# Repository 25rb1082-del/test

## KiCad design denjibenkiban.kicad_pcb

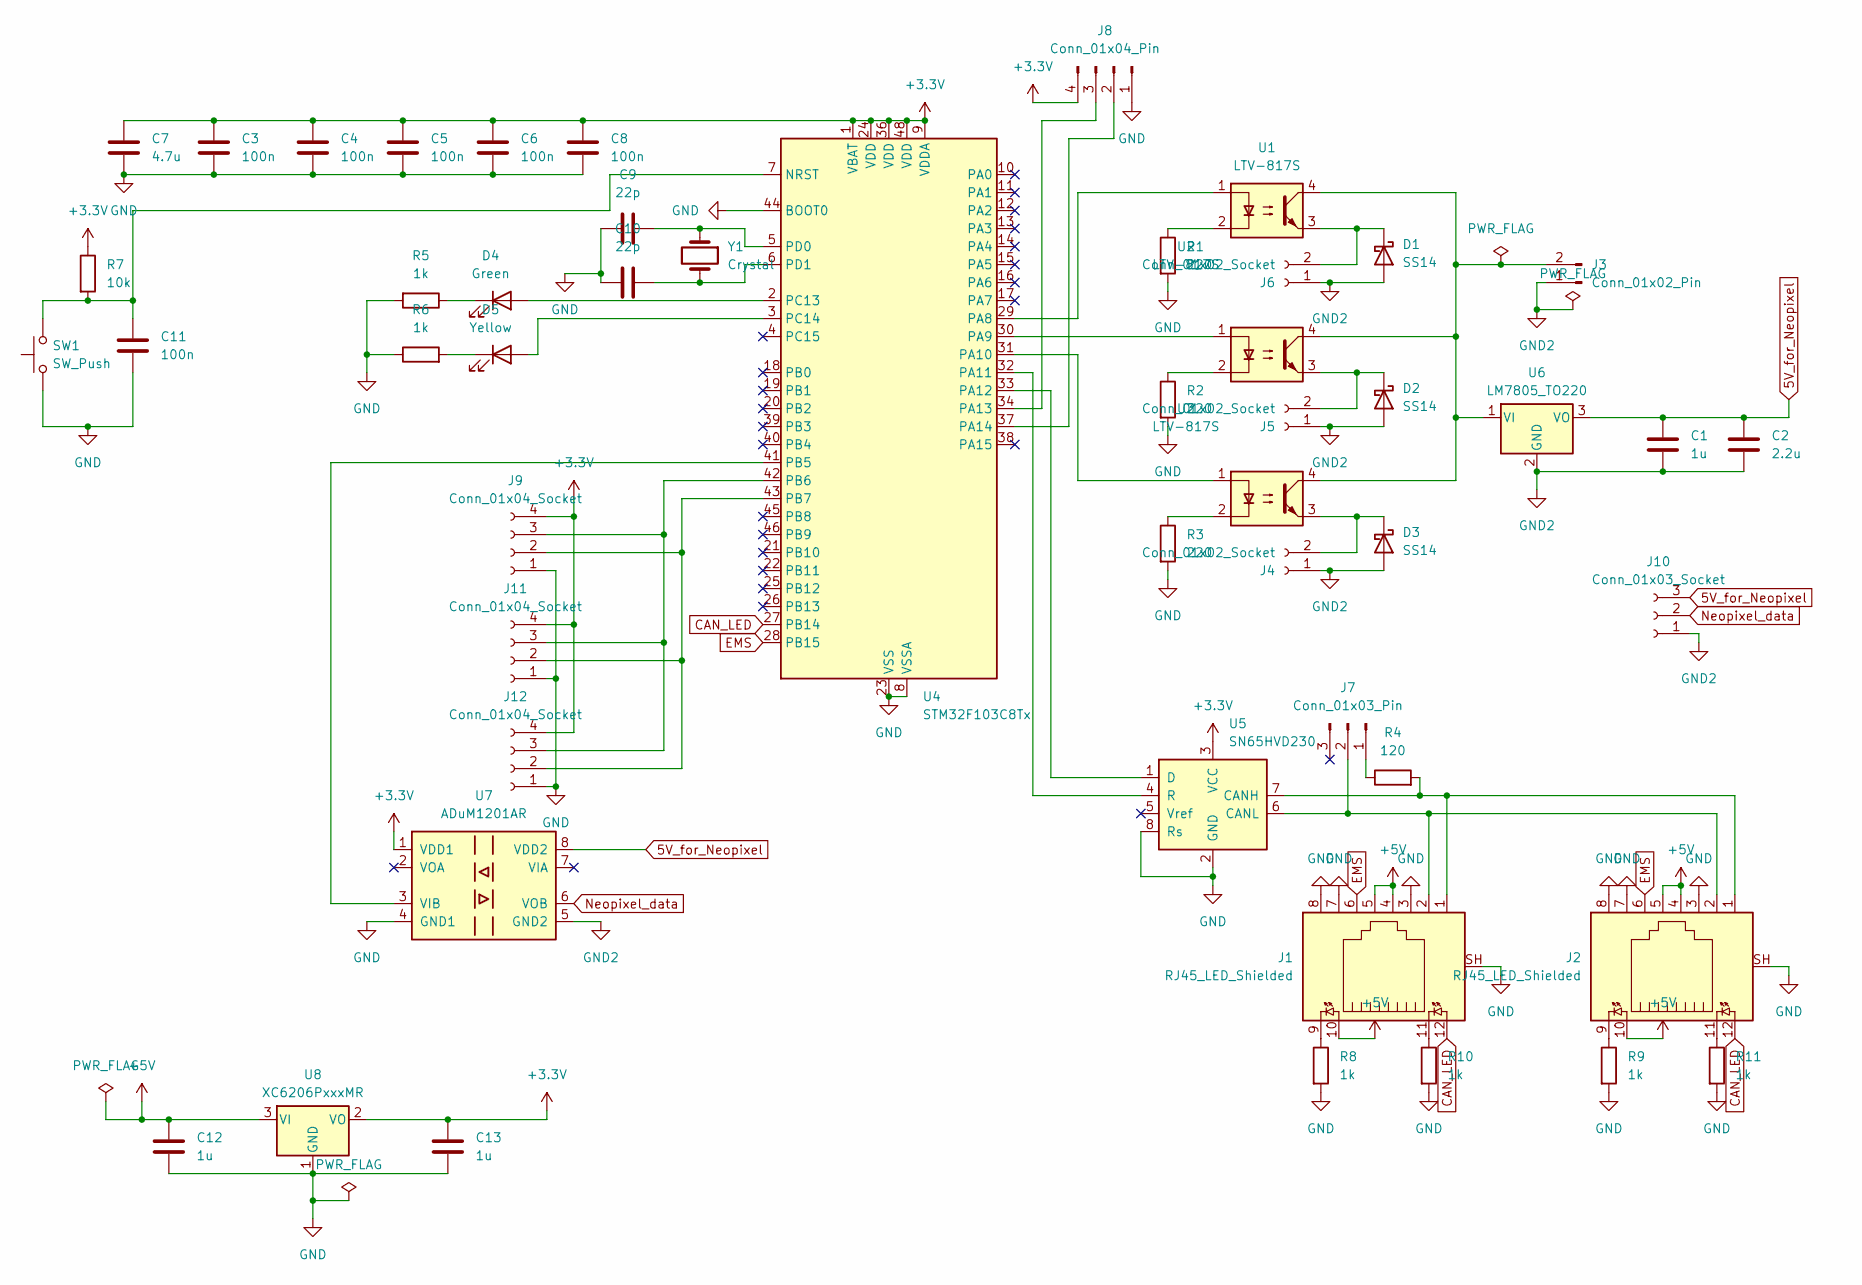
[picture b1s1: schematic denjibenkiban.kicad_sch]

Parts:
C1, C12, C13: 1u; C_0603_1608Metric
C2: 2.2u; C_0603_1608Metric
C3, C4, C5, C6, C8, C11: 100n; C_0603_1608Metric
C7: 4.7u; C_0603_1608Metric
C9, C10: 22p; C_0603_1608Metric
D1, D2, D3: SS14; D_SMA
D4: Green; LED_0805_2012Metric
D5: Yellow; LED_0805_2012Metric
J1, J2: RJ45_LED_Shielded; RJ45_Amphenol_RJHSE538X
J3: Conn_01x02_Pin; AMASS_XT30U-F_1x02_P5.0mm_Vertical
J4, J5, J6: Conn_01x02_Socket; JST_XH_B2B-XH-A_1x02_P2.50mm_Vertical
J7: Conn_01x03_Pin; PinHeader_1x03_P2.54mm_Vertical
J8: Conn_01x04_Pin; PinHeader_1x04_P2.54mm_Vertical
J9, J11, J12: Conn_01x04_Socket; JST_XH_B4B-XH-A_1x04_P2.50mm_Vertical
J10: Conn_01x03_Socket; JST_XH_B3B-XH-A_1x03_P2.50mm_Vertical
R1, R2, R3: 220; R_0603_1608Metric
R4: 120; R_0603_1608Metric
R5, R6, R8, R9, R10, R11: 1k; R_0603_1608Metric
R7: 10k; R_0603_1608Metric
SW1: SW_Push; SW_TS-1088-AR02016
U1, U2, U3: LTV-817S; SMDIP-4_W9.53mm
U4: STM32F103C8Tx; LQFP-48_7x7mm_P0.5mm
U5: SN65HVD230; SOIC-8_3.9x4.9mm_P1.27mm
U6: LM7805_TO220; TO-220-3_Vertical
U7: ADuM1201AR; SOIC-8_3.9x4.9mm_P1.27mm
U8: XC6206PxxxMR; SOT-23-3
Y1: Crystal; Crystal_SMD_5032-2Pin_5.0x3.2mm

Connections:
5V_for_Neopixel: C1.1, C2.1, J10.3, U6.3 (VO), U7.8 (VDD2)
+3.3V: C3.1, C4.1, C5.1, C6.1, C7.1, C8.1, C13.1, J8.4, J9.4, J11.4, J12.4, R7.1, U4.1 (VBAT), U4.9 (VDDA), U4.24 (VDD), U4.36 (VDD), U4.48 (VDD), U5.3 (VCC), U7.1 (VDD1), U8.2 (VO)
+5V: C12.1, J1.4, J1.5, J1.10, J2.4, J2.5, J2.10, U8.3 (VI)
CAN_LED: J1.12, J2.12, U4.27 (PB14)
EMS: J1.6, J2.6, U4.28 (PB15)
GND: C3.2, C4.2, C5.2, C6.2, C7.2, C8.2, C9.2, C10.2, C11.1, C12.2, C13.2, J1.3, J1.7, J1.8, J1.SH, J2.3, J2.7, J2.8, J2.SH, J8.1, J9.1, J11.1, J12.1, R1.2, R2.2, R3.2, R5.2, R6.1, R8.2, R9.2, R10.2, R11.2, SW1.1, U4.8 (VSSA), U4.23 (VSS), U4.35 (VSS), U4.44 (BOOT0), U4.47 (VSS), U5.2 (GND), U5.8 (Rs), U7.4 (GND1), U8.1 (GND)
GND2: C1.2, C2.2, D1.2 (A), D2.2 (A), D3.2 (A), J3.1, J4.1, J5.1, J6.1, J10.1, U6.2 (GND), U7.5 (GND2)
Neopixel_data: J10.2, U7.6 (VOB)
unnamed: D1.1 (K), J6.2, U1.3
unnamed: D2.1 (K), J5.2, U2.3
unnamed: D3.1 (K), J4.2, U3.3
unnamed: D4.2 (A), U4.2 (PC13)
unnamed: D4.1 (K), R5.1
unnamed: D5.2 (A), U4.3 (PC14)
unnamed: D5.1 (K), R6.2
unnamed: J1.9, R8.1
unnamed: J1.11, R10.1
unnamed: J2.9, R9.1
unnamed: J2.11, R11.1
unnamed: J3.2, U1.4, U2.4, U3.4, U6.1 (VI)
unnamed: J7.1, R4.1
unnamed: J1.2, J2.2, J7.2, U5.6 (CANL)
unnamed: J8.2, U4.37 (PA14)
unnamed: J8.3, U4.34 (PA13)
unnamed: J9.2, J11.2, J12.2, U4.43 (PB7)
unnamed: J9.3, J11.3, J12.3, U4.42 (PB6)
unnamed: R1.1, U1.2
unnamed: R2.1, U2.2
unnamed: R3.1, U3.2
unnamed: C11.2, R7.2, SW1.2, U4.7 (NRST)
unnamed: U1.1, U4.29 (PA8)
unnamed: U2.1, U4.30 (PA9)
unnamed: U3.1, U4.31 (PA10)
unnamed: U4.32 (PA11), U5.4 (R)
unnamed: U4.33 (PA12), U5.1 (D)
unnamed: U4.41 (PB5), U7.3 (VIB)
unnamed: C9.1, U4.5 (PD0), Y1.1
unnamed: C10.1, U4.6 (PD1), Y1.2
unnamed: J1.1, J2.1, R4.2, U5.7 (CANH)

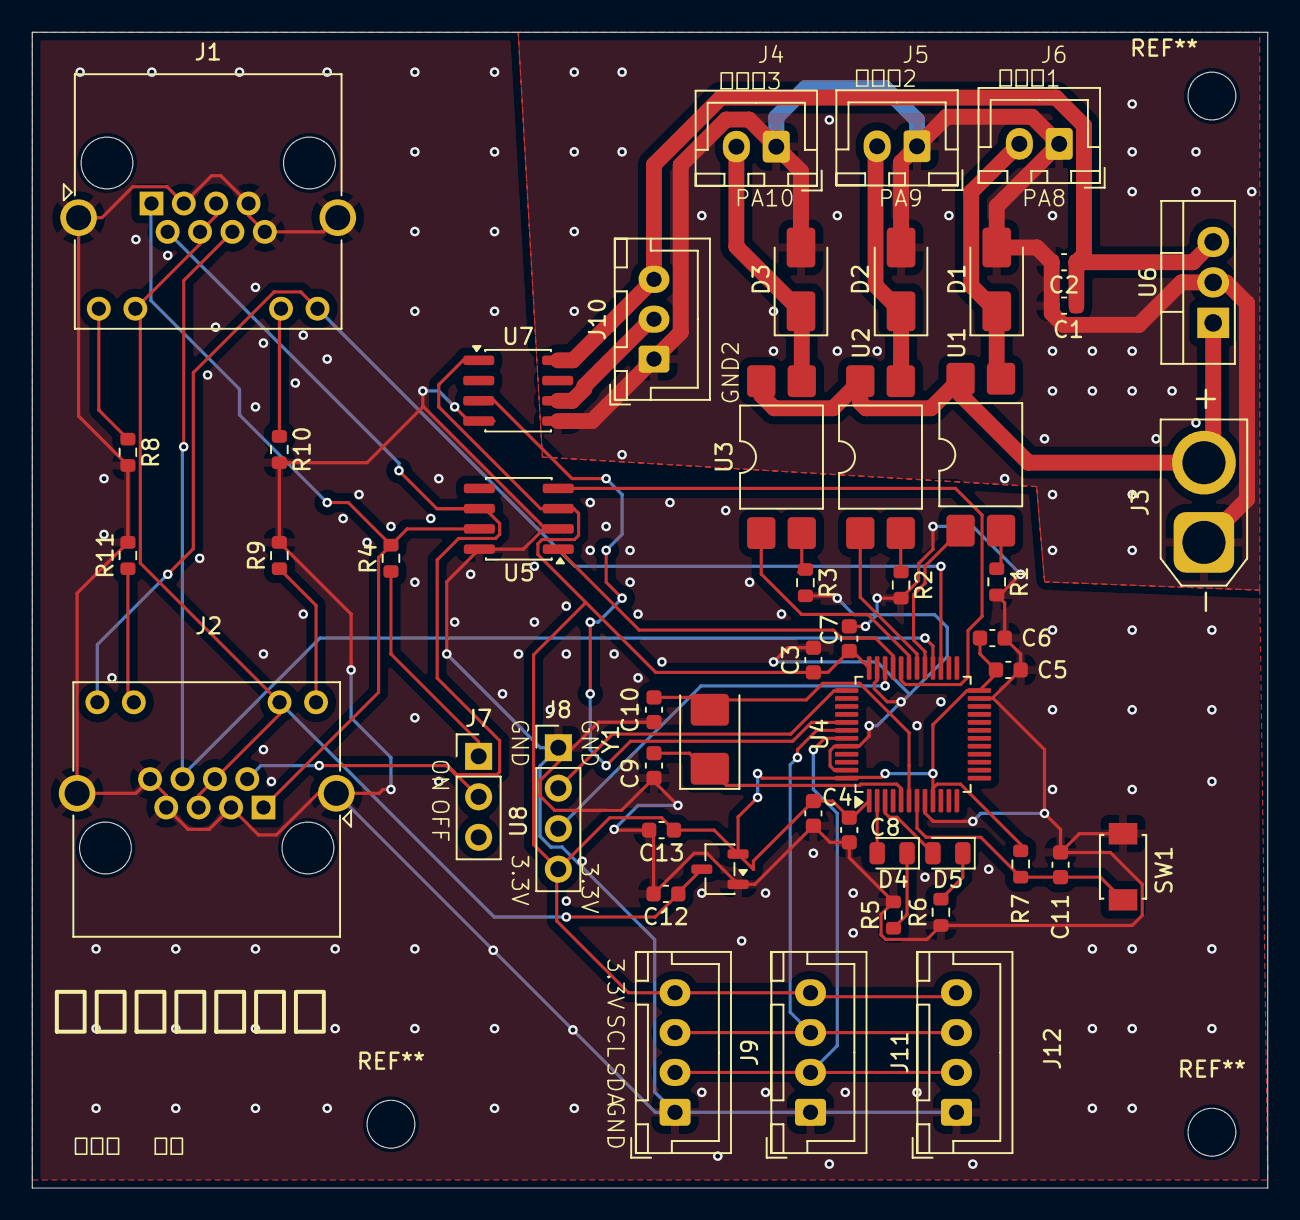
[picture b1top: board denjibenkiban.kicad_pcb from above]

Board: 2 copper layers, 77.5 x 72.5 mm, 51 parts (0 on the bottom side), 39 nets.
